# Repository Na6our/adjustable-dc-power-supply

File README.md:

# Adjustable DC Power Supply (LM317)

A small bench supply built around the LM317: 15 V DC in, adjustable output, on a 40 × 40 mm board. Designed and verified in LTspice, PCB layout in KiCad.

**Status:** simulation, thermal design and PCB layout done. Not built yet. A test version with locally available parts is described under [Build variant](#build-variant).

## Spec

| | |
|---|---|
| Input | 15 V DC wall adapter |
| Output | 1.25 V to 11.8 V |
| Max current | 1 A above 9.3 V out, derated below that (see Thermal) |
| Board | 40 × 40 mm |

## Repository

```
simulation/            LTspice files (.asc)
images/                plots and measurement logs
kicad/original/        original design: schematic, PCB, footprints, Gerbers
kicad/build_variant/   test build with locally available parts
```

## Circuit

The LM317 keeps 1.25 V between OUT and ADJ, so R1 carries a fixed 5.2 mA and the pot (RV1) sets the output:

```
Vout = 1.25 V × (1 + RV1/R1) + I_ADJ × RV1
```

| Part | Value | Why |
|---|---|---|
| R1 | 240 Ω | Sets 5.2 mA through the divider, which also covers the LM317's minimum load current |
| RV1 | 2 kΩ pot (Alps RK09K) | Sets the output. Limited to 2 kΩ because of dropout (see below) |
| C1 | 0.1 µF | Input decoupling |
| C2 | 10 µF, 105 °C | Output. 0.1 µF oscillated at 1 A in simulation |
| C3 | 10 µF, 105 °C | ADJ bypass, improves ripple rejection |
| D1, D2 | 1N4002 | Give the capacitors a safe discharge path if the input or output is shorted (1N4148 in simulation) |

*Figure 1: KiCad schematic.*

In the simulations the pot is called R2. All measurements were taken with LTspice `.meas` statements (screenshots of the logs are collapsed at the bottom).

## Results

### Compared with a discrete regulator

Before the LM317 I simulated a Zener + emitter-follower regulator (4.7 V Zener, 2N2222, 240 Ω feed resistor) to see what a regulator without feedback does. Both were set to about 4 V out.

| | Zener + transistor | LM317 |
|---|---|---|
| Load regulation, 4 to 80 mA | 2.51 % | 0.0033 % |
| Line regulation, 12 to 18 V in | 5.88 mV/V | 0.079 mV/V |
| Drift, −20 to 85 °C | 152.9 mV | 0.40 mV |

The Zener circuit sags under load because V_BE rises with current and the base current is taken from the Zener. Nothing corrects it. The LM317 compares its output against an internal reference and is two to three orders of magnitude better on every test.

The simulated LM317 also beats its own datasheet (typically 0.1 % load and 0.01 %/V line regulation). The SPICE model leaves out self-heating, lead resistance and part-to-part spread, so a real board will be worse.

*Figure 2: Zener regulator output for loads from 50 Ω to 1 kΩ. The output drops about 100 mV as the load increases.*

*Figure 3: Zener regulator output for 12, 15 and 18 V input.*

*Figure 4: Zener regulator output at −20 °C and 25 °C. The 85 °C trace (4.066 V) is above the plotted window.*

### Output range

Sweeping R2 from 10 Ω to 2.2 kΩ gave 1.3 V to 12.9 V, matching the formula. The model ran about 0.5 % high: measuring it directly gave a reference of 1.2569 V and an ADJ current of 47.5 µA, and with those values the formula matches the simulation exactly. A real LM317's reference can be anywhere from 1.20 to 1.30 V, so the pot takes care of this.

*Figure 5: LM317 output for R2 from 10 Ω to 2.2 kΩ (15 V in, 100 Ω load).*

### Load step

Load stepped from 10 mA to 1 A and back.

| C2 | Dip at 1 A step | Overshoot on release |
|---|---|---|
| 0.1 µF | oscillates continuously | |
| 1 µF | −256 mV | +177 mV |
| 10 µF | −148 mV | +108 mV |

The steady output changed by only 0.33 mV between 10 mA and 1 A. With 0.1 µF the regulator oscillated between 3.6 and 4.4 V for the whole time the load was on, which matches the datasheet's warning about small output capacitors. I went with 10 µF.

*Figure 6: Load step with C2 = 1 µF. Short dip when 1 A is applied at 10 ms, overshoot when it is released at 15 ms.*

*Figure 7: The same step with C2 = 0.1 µF (green, oscillating), 1 µF (blue) and 10 µF (red).*

### Ripple rejection

2 V p-p of 100 Hz ripple on the input.

| C3 | Output ripple | Rejection |
|---|---|---|
| none | 168.8 µV | 81.5 dB |
| 10 µF | 69.1 µV | 89.2 dB |

Without C3, ripple at ADJ is amplified by the divider gain (1 + R2/R1 = 3.2, or 10 dB). C3 removes that, so 10 dB is the most it can help at this output, and it gave 7.8 dB. The gain is higher at higher output voltages, so C3 matters more there.

*Figure 8: Output ripple without C3 (green) and with C3 = 10 µF (blue).*

### Dropout

Input ramped down from 18 V with the output set to 12.88 V.

| Load | Dropout |
|---|---|
| 0.1 A | 1.88 V |
| 0.5 A | 2.05 V |
| 1 A | 2.23 V |

At 1 A the top setting needs 15.01 V in, and a real LM317 needs up to about 2.5 V. A 15 V adapter can't hold 12.9 V, so R2 is capped at 2 kΩ, giving 11.8 V max. That needs about 14.3 V at 1 A with real-world dropout, which still works if the adapter is 5 % low.

*Figure 9: Output (green) and input-output difference (blue) as the input ramps from 18 V down to 10 V, for 0.1, 0.5 and 1 A. Time runs left to right, so the input falls left to right.*

### Thermal

The LM317 dissipates (Vin − Vout) × I. Worst case is 13.75 W (1.25 V out at 1 A), which would need a heatsink much bigger than the board.

Heatsink: Assmann WSW V6560W (DigiKey AE10901-ND), 10 K/W, stands upright with a 30 × 12 mm footprint. TI gives RθJC = 0.1 °C/W for the tab. I designed with a more conservative 4 °C/W plus 1 °C/W for the thermal pad, which limits dissipation to 5.7 W at 40 °C ambient. With TI's figure the junction would sit around 103 °C at that limit, leaving margin below 125 °C.

| Output | Max current |
|---|---|
| 1.25 V | 0.41 A |
| 5 V | 0.57 A |
| 9 V | 0.94 A |
| 9.3 V and up | 1 A |

Above these limits the LM317's thermal shutdown kicks in.

The TO-220 tab is connected to OUT, so the heatsink sits at the output voltage. Its pins can't go to ground on the PCB, and it shouldn't touch anything grounded, like a metal case or a scope ground clip.

## PCB

Two-layer, 40 × 40 mm, all through-hole so it can be hand-soldered. Layout choices:

- The heatsink sits along the top edge with the LM317 standing against its flat face. Everything else is arranged around that pair.
- Input comes in on the right (J1), straight into C1 and the LM317's IN pin. Output leaves on the left (J2) on a direct track from the OUT pin.
- R1 sits right under the LM317 with its own track to the OUT pin, so load current doesn't flow through the feedback path. The datasheet asks for this.
- IN, OUT and GND use 1.0 mm tracks (about 0.3 mm would do for 1 A on 1 oz copper). ADJ uses 0.5 mm.
- The bottom layer is a solid GND pour, so ground needs no tracks.
- The heatsink's pins are on the OUT net, since the LM317's tab is connected to OUT. That keeps the ground pour clear of them.
- Two M3 mounting holes along the bottom edge.

The heatsink footprint (Assmann V6560W) isn't in KiCad's library, so I drew it from the datasheet drawing (ASS 0595 HS): pins 25.4 mm apart, Ø 2.7 mm holes, 30 × 12 mm outline.

Changes from the simulation: the protection diodes are 1N4002 instead of 1N4148, because on a real board they have to carry the capacitors' discharge current, and the datasheet suggests 1N4002-type parts. C2 and C3 should be 105 °C electrolytics, since they sit close to the regulator.

*Figure 10: 3D render, top. The heatsink has no 3D model, so only its outline shows.*

*Figure 11: 3D render, bottom, with the ground pour and board label.*

## Build variant

The heatsink and the pot above aren't available in Jordan, so for a test build I swapped them for parts I could buy locally and made a second version of the board.

| | Original design | Build variant |
|---|---|---|
| Heatsink | Assmann V6560W, 10 K/W, soldered to the PCB | Clip-on TO-220 heatsink, 15 × 10 × 20 mm (Mikroelectron ME-13388), no pins |
| Pot | 2 kΩ, Alps RK09K panel-style | 1 kΩ multi-turn trimmer (3296W-style) |
| R1 | 240 Ω | 100 Ω (120 Ω wasn't available) |
| Output range | 1.25 to 11.8 V | 1.25 V up to about 12.5 V regulated; the pot's last turns go past what 15 V in can regulate |
| Max dissipation | 5.7 W | about 2.8 W |
| Max current | 0.41 A at 1.25 V, 1 A from 9.3 V | 0.21 A at 1.25 V, 0.86 A at 11.7 V |

The cost is power handling. The clip-on heatsink has no published rating, and heatsinks that size are typically around 20 to 25 °C/W. Assuming 25 °C/W, the regulator can only get rid of about half as much heat, so the current it can deliver drops by about half at every output voltage, and 1 A is no longer reachable. Regulation itself is unaffected, and the lower R1 raises the divider current to 12.5 mA, which meets the LM317's worst-case 10 mA minimum load.

With R1 = 100 Ω, full scale on the pot would be about 13.8 V. The dropout test showed the LM317 needs about 1.9 to 2.2 V (and a real part up to about 2.5 V), so from a 15 V input it only regulates up to roughly 12.5 V. Above that the output just follows the input, so the top of the pot's range is avoided. 120 Ω would have kept the full range usable (11.7 V max), but I couldn't source one.

*Figure 12: Build variant layout. The trimmer is in the bottom-left corner and the heatsink outline sits behind the LM317's tab.*

*Figure 13: Build variant, 3D render.*

## Next steps

- [ ] Re-run the output range simulation for the build variant (R1 = 100 Ω, 1 kΩ pot) and find where it drops out
- [ ] Order the build variant boards and parts, build and test against the simulation
- [ ] If built: measure the heatsink's real thermal resistance

<details>
<summary>Measurement logs</summary>

</details>

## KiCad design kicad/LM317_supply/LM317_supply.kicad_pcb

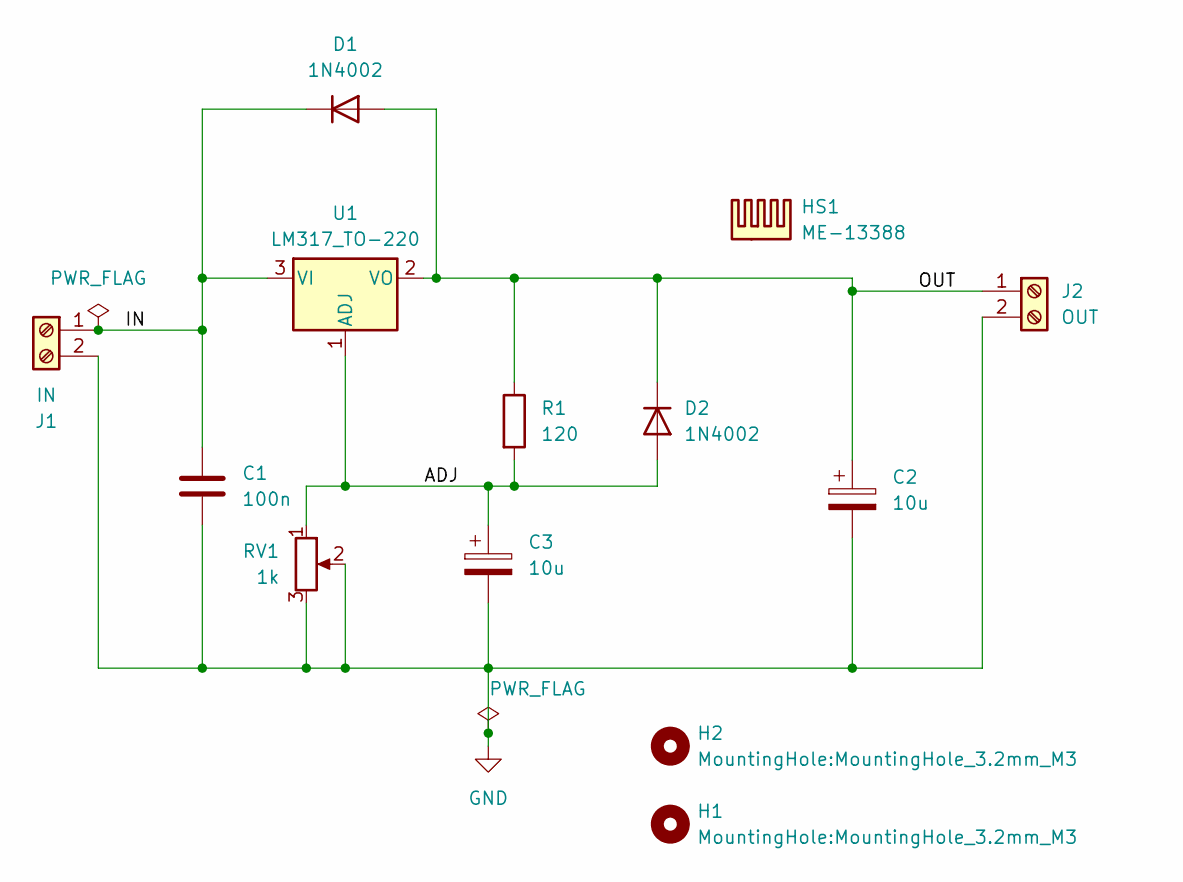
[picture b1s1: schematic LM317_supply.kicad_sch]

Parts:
C1: 100n; C_Disc_D5.0mm_W2.5mm_P5.00mm
C2, C3: 10u; CP_Radial_D5.0mm_P2.00mm
D1, D2: 1N4002; D_DO-41_SOD81_P10.16mm_Horizontal
H1, H2: MountingHole:MountingHole_3.2mm_M3; MountingHole_3.2mm_M3
HS1: ME-13388; Heatsink_TO220_15x10
J1: IN; TerminalBlock_Phoenix_MKDS-1,5-2-5.08_1x02_P5.08mm_Horizont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
J2: OUT; TerminalBlock_Phoenix_MKDS-1,5-2-5.08_1x02_P5.08mm_Horizont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
R1: 120; R_Axial_DIN0207_L6.3mm_D2.5mm_P10.16mm_Horizontal
RV1: 1k; Potentiometer_Bourns_3296P_Horizontal
U1: LM317_TO-220; TO-220-3_Vertical

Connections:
/ADJ: C3.1, D2.2 (A), R1.2, RV1.1, U1.1 (ADJ)
/IN: C1.1, D1.1 (K), J1.1, U1.3 (VI)
/OUT: C2.1, D1.2 (A), D2.1 (K), J2.1, R1.1, U1.2 (VO)
GND: C1.2, C2.2, C3.2, J1.2, J2.2, RV1.2, RV1.3

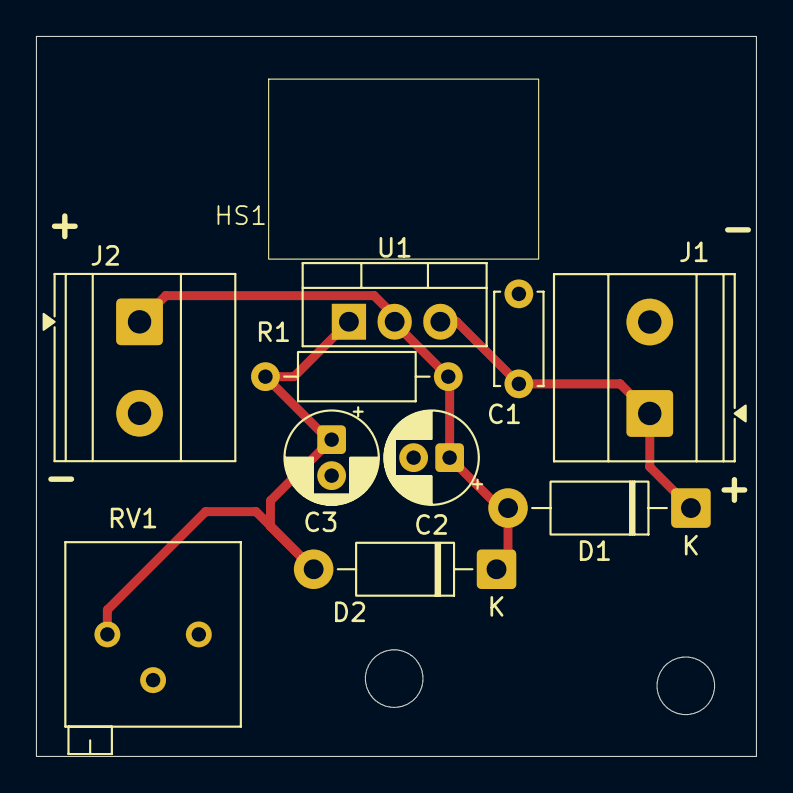
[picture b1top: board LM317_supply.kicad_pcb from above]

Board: 2 copper layers, 40.0 x 40.0 mm, 13 parts (0 on the bottom side), 4 nets.
